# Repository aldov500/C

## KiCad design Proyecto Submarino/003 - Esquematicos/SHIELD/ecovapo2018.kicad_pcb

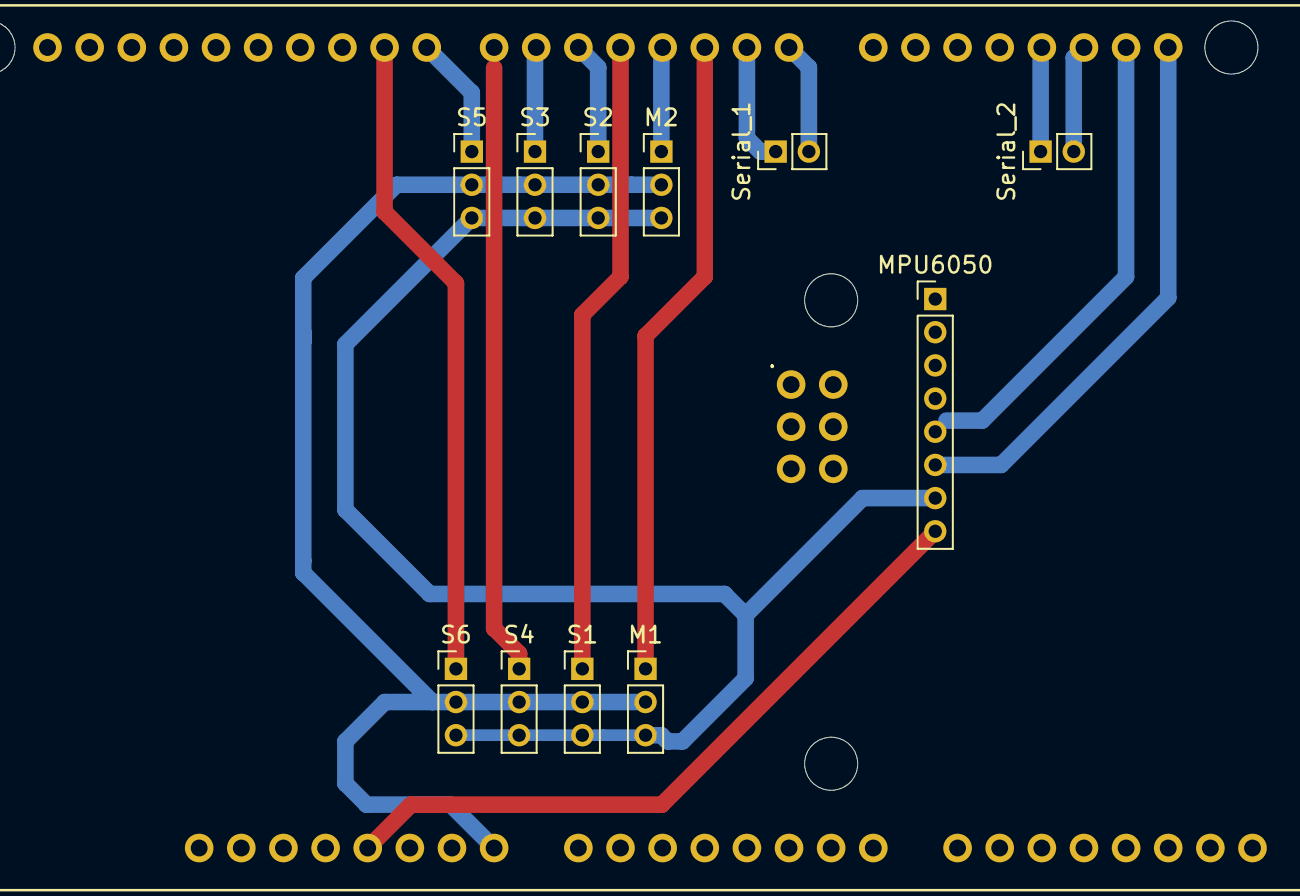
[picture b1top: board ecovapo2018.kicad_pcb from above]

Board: 2 copper layers, 12 parts (0 on the bottom side), 17 nets.

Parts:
M1, M2: Conn_01x03; PinHeader_1x03_P2.00mm_Vertical
MPU6050: Conn_01x08; PinHeader_1x08_P2.00mm_Vertical
S1, S2, S3, S4, S5, S6: Conn_01x03; PinHeader_1x03_P2.00mm_Vertical
Serial_1, Serial_2: Conn_01x02; PinHeader_1x02_P2.00mm_Vertical
XA1: Arduino_Mega2560_Shield

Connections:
GND: M1.3, M2.3, MPU6050.7, S1.3, S2.3, S3.3, S4.3, S5.3, S6.3, XA1.GND1
unnamed: M1.1, XA1.D2
unnamed: M1.2, M2.2, S1.2, S2.2, S3.2, S4.2, S5.2, S6.2, XA1.VIN
unnamed: M2.1, XA1.D3
unnamed: MPU6050.5, XA1.D20
unnamed: MPU6050.6, XA1.D21
unnamed: MPU6050.8, XA1.5V1
unnamed: S1.1, XA1.D4
unnamed: S2.1, XA1.D5
unnamed: S3.1, XA1.D6
unnamed: S4.1, XA1.D7
unnamed: S5.1, XA1.D8
unnamed: S6.1, XA1.D9
unnamed: Serial_1.1, XA1.D1
unnamed: Serial_1.2, XA1.D0
unnamed: Serial_2.1, XA1.D18
unnamed: Serial_2.2, XA1.D19

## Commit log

2021-04-04 Agregado KL25Z al repositorio
2021-04-04 Agregado STM32F429
2021-04-04 C for PIC
2021-04-05 Topicos selectos add
